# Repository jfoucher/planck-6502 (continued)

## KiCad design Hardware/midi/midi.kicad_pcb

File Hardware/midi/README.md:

## Planck 6502 MIDI board

This is a board that adds MIDI input / output to the Planck 6502 computer.

<br />This documentation is licensed under a <a rel="license" href="http://creativecommons.org/licenses/by-sa/4.0/">Creative Commons Attribution-ShareAlike 4.0 International License</a>.

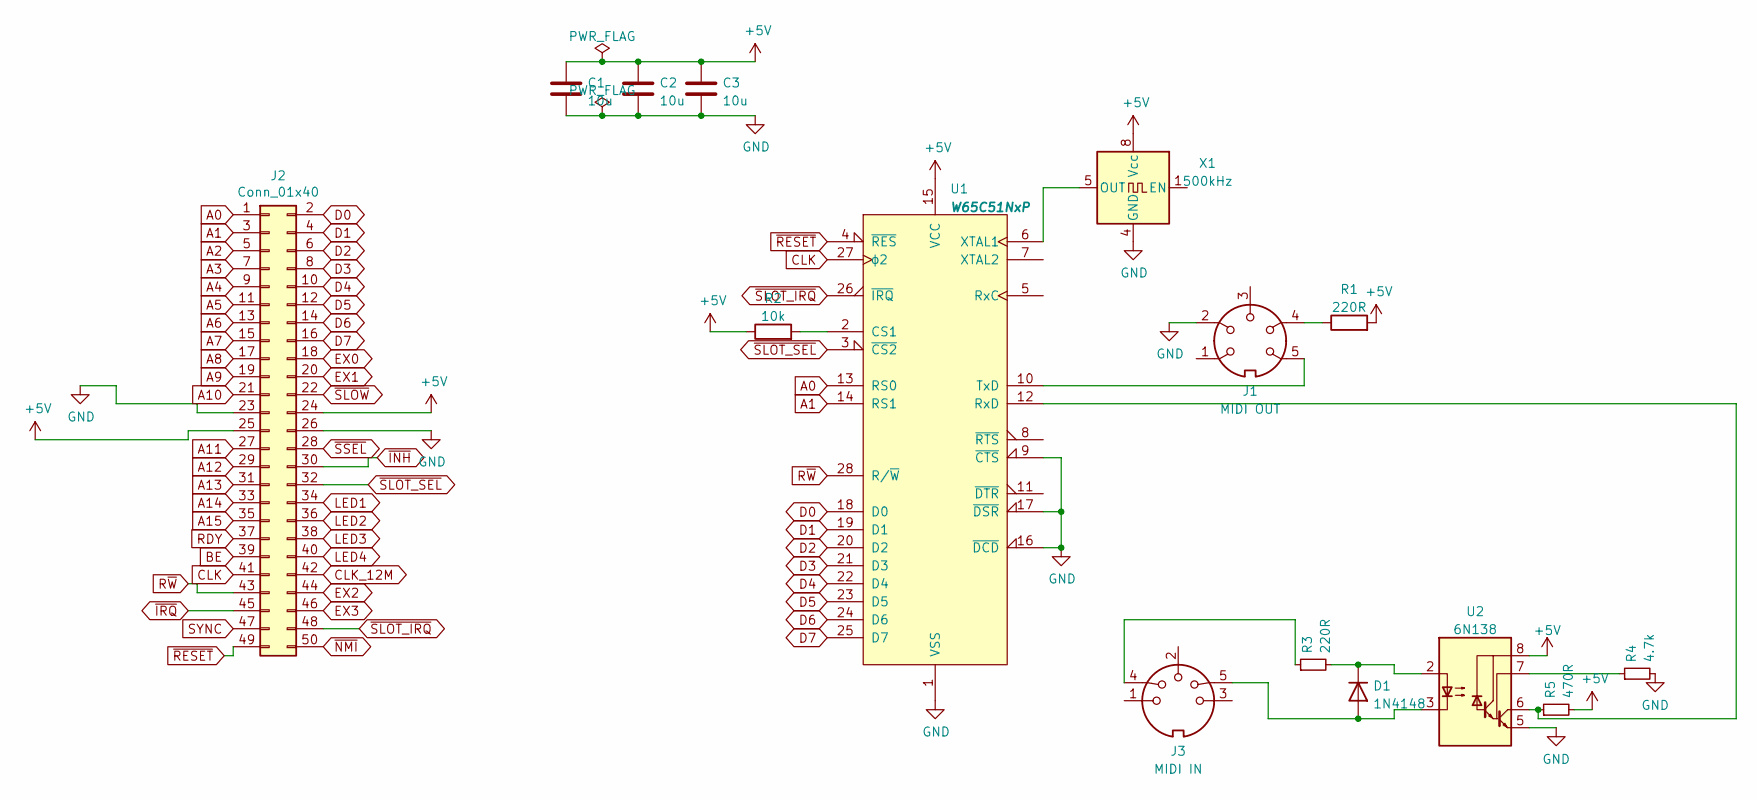
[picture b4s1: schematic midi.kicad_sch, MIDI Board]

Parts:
C1, C2, C3: 10u; C_Disc_D5.1mm_W3.2mm_P5.00mm
D1: 1N4148; D_DO-35_SOD27_P7.62mm_Horizontal
J1: MIDI OUT; din-5
J2: Conn_01x40; PinHeader_2x25_P2.54mm_Horizontal
J3: MIDI IN; din-5
R1, R3: 220R; R_Axial_DIN0207_L6.3mm_D2.5mm_P10.16mm_Horizontal
R2: 10k; R_Axial_DIN0207_L6.3mm_D2.5mm_P10.16mm_Horizontal
R4: 4.7k; R_Axial_DIN0207_L6.3mm_D2.5mm_P10.16mm_Horizontal
R5: 470R; R_Axial_DIN0207_L6.3mm_D2.5mm_P10.16mm_Horizontal
U1: W65C51NxP; DIP-40_W15.24mm_Socket
U2: 6N138; DIP-8_W7.62mm
X1: 500kHz; Oscillator_DIP-8

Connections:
+5V: C1.1, C2.1, C3.1, J2.24, J2.25, R1.2, R2.1, R5.2, U1.15 (VCC), U2.8 (VCC), X1.8 (Vcc)
A0: J2.1, U1.13 (RS0)
A1: J2.3, U1.14 (RS1)
A2: J2.5
A3: J2.7
A4: J2.9
A5: J2.11
A6: J2.13
A7: J2.15
A8: J2.17
A9: J2.19
A10: J2.21
A11: J2.27
A12: J2.29
A13: J2.31
A14: J2.33
A15: J2.35
BE: J2.39
CLK: J2.41, U1.27 (ϕ2)
CLK_12M: J2.42
D0: J2.2, U1.18 (D0)
D1: J2.4, U1.19 (D1)
D2: J2.6, U1.20 (D2)
D3: J2.8, U1.21 (D3)
D4: J2.10, U1.22 (D4)
D5: J2.12, U1.23 (D5)
D6: J2.14, U1.24 (D6)
D7: J2.16, U1.25 (D7)
EX0: J2.18
EX1: J2.20
EX2: J2.44
EX3: J2.46
GND: C1.2, C2.2, C3.2, J1.2, J2.23, J2.26, R4.2, U1.1 (VSS), U1.9 (~CTS), U1.16 (~DCD), U1.17 (~DSR), U2.5 (GND), X1.4 (GND)
LED1: J2.34
LED2: J2.36
LED3: J2.38
LED4: J2.40
unnamed: D1.1 (K), R3.2, U2.2 (C1)
unnamed: D1.2 (A), J3.5, U2.3 (C2)
unnamed: J1.4, R1.1
unnamed: J1.5, U1.10 (TxD)
unnamed: J3.4, R3.1
unnamed: R2.2, U1.2 (CS1)
unnamed: R4.1, U2.7 (VO1)
unnamed: R5.1, U1.12 (RxD), U2.6 (VO2)
unnamed: U1.6 (XTAL1), X1.5 (OUT)
RDY: J2.37
R~W: J2.43, U1.28 (R/~W)
SYNC: J2.47
~INH: J2.30
~IRQ: J2.45
~NMI: J2.50
~RESET: J2.49, U1.4 (~RES)
~SLOT_IRQ: J2.48, U1.26 (~IRQ)
~SLOT_SEL: J2.32, U1.3 (~CS2)
~SLOW: J2.22
~SSEL: J2.28

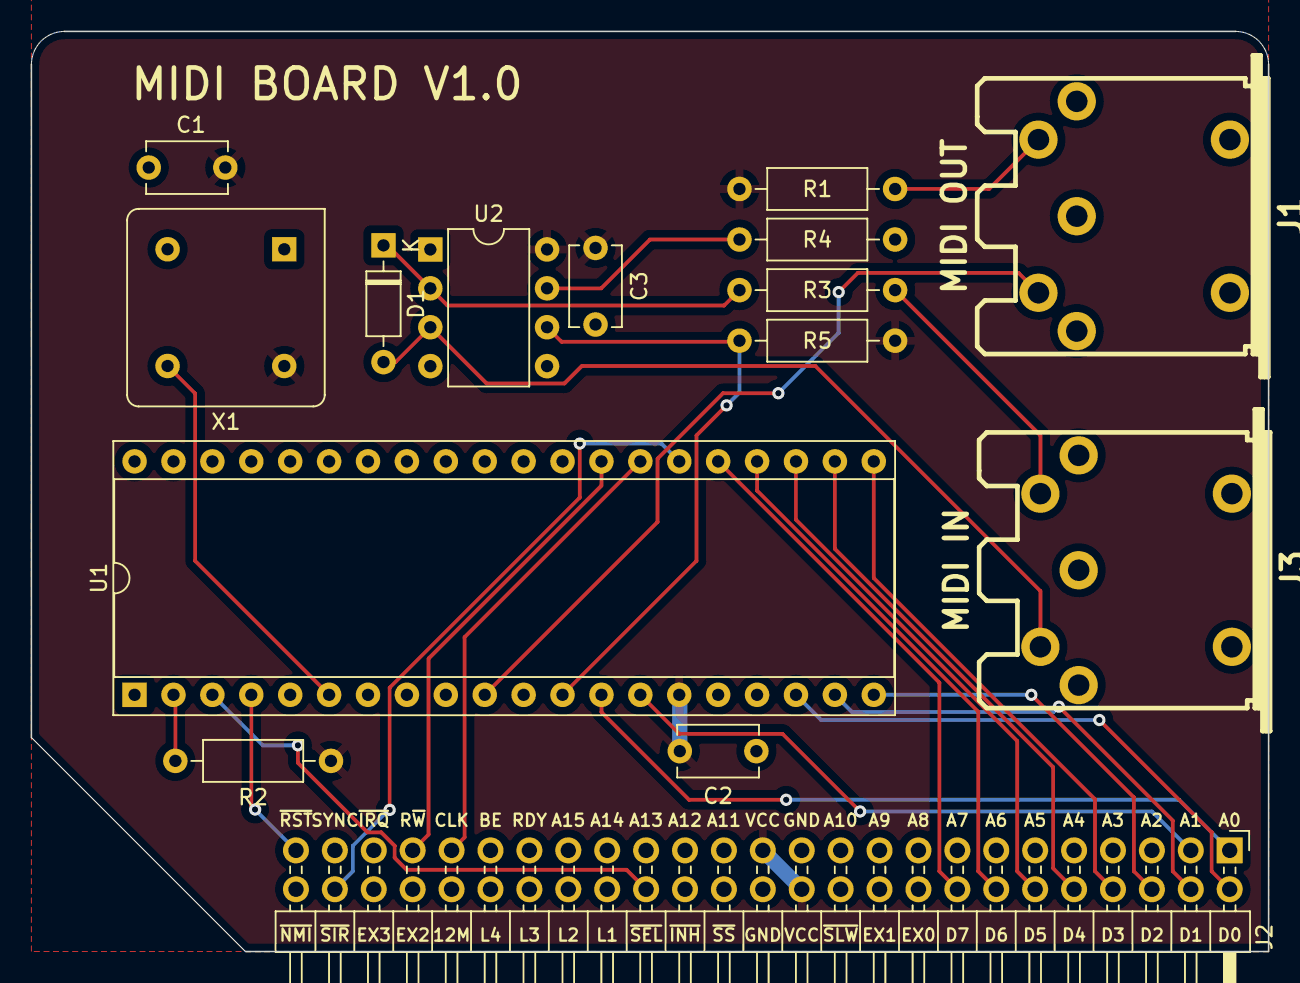
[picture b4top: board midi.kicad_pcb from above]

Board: 2 copper layers, 80.8 x 60.1 mm, 15 parts (0 on the bottom side), 26 nets.

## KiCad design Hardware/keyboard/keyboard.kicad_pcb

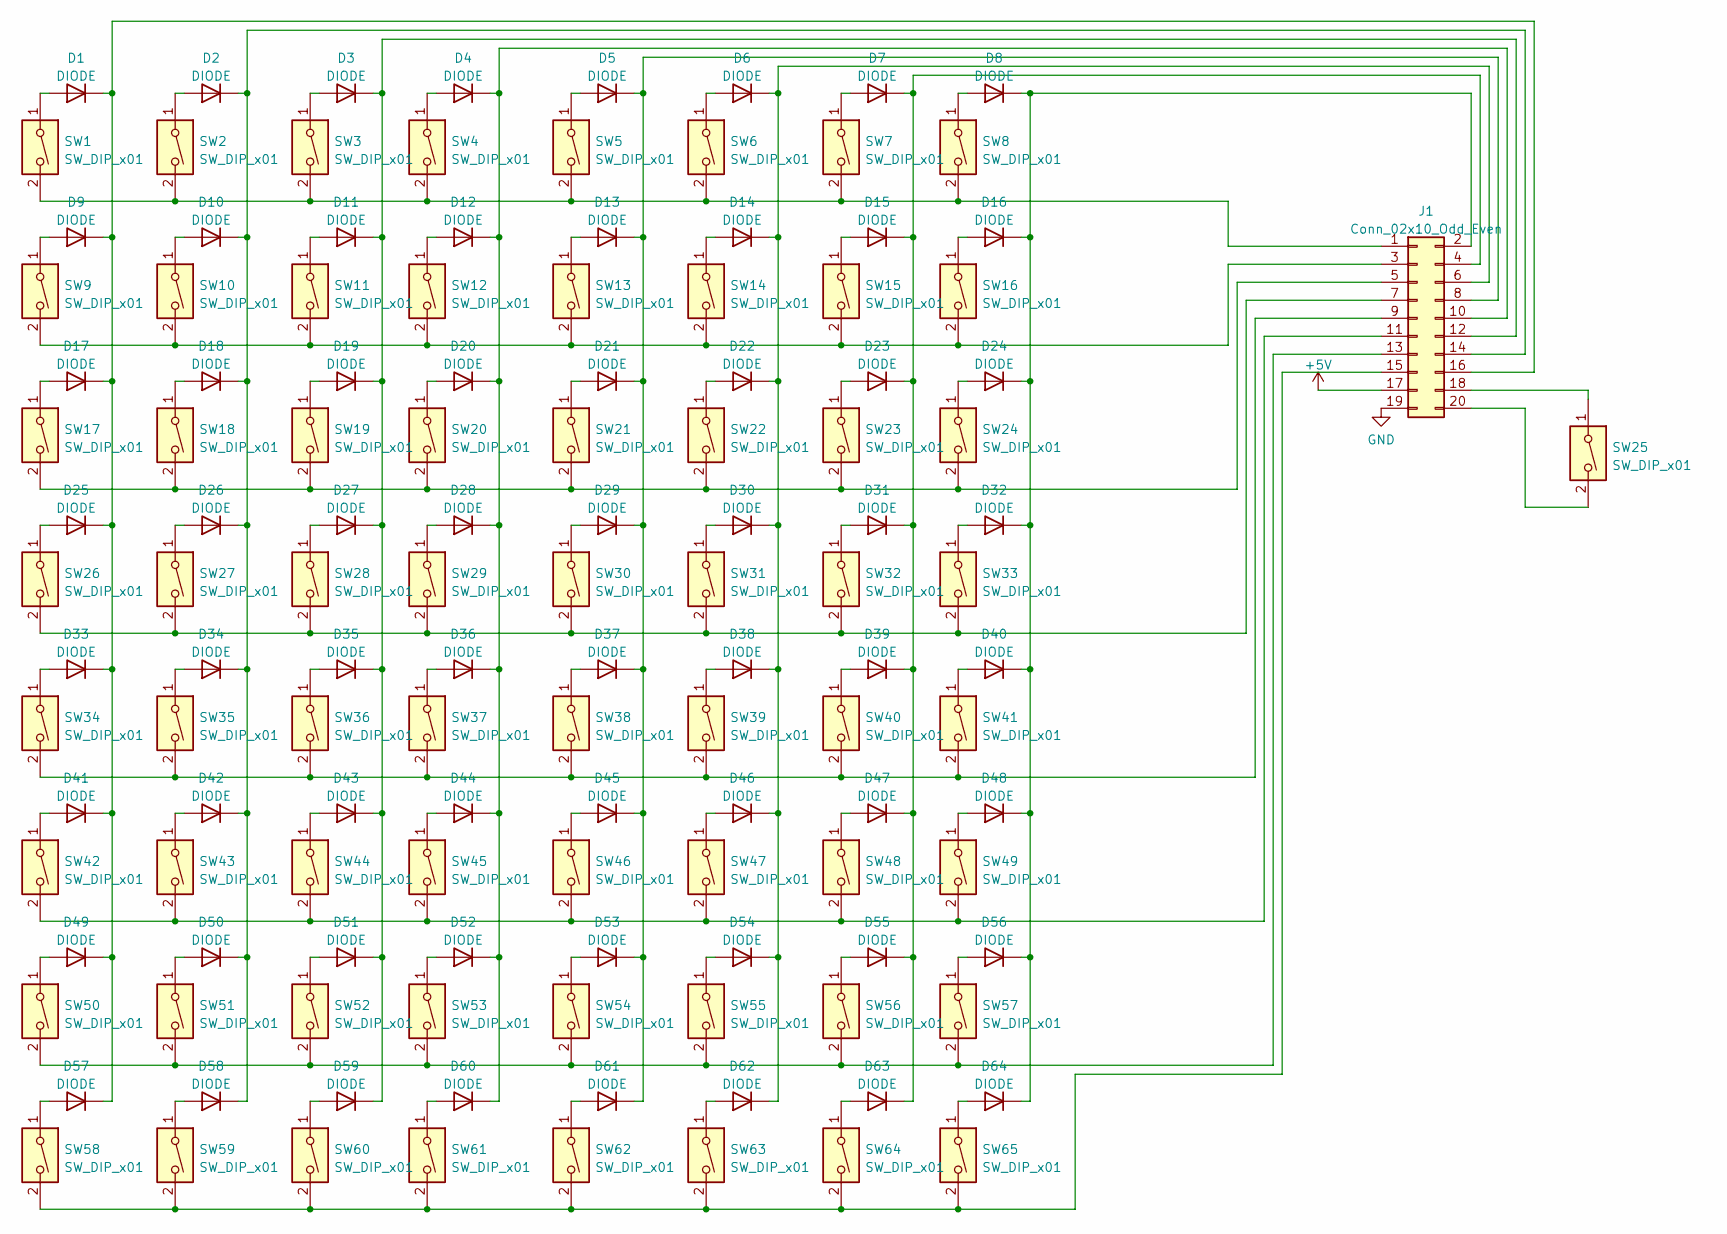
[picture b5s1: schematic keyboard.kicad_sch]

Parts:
D1, D2, D3, D4, D5, D6, D7, D8, D9, D10, D11, D12, D13, D14, D15, D16, D17, D18, D19, D20, D21, D22, D23, D24, D25, D26, D27, D28, D29, D30, D31, D32, D33, D34, D35, D36, D37, D38, D39, D40, D41, D42, D43, D44, D45, D46, D47, D48, D49, D50, D51, D52, D53, D54, D55, D56, D57, D58, D59, D60, D61, D62, D63, D64: DIODE; D_DO-35_SOD27_P7.62mm_Horizontal
J1: Conn_02x10_Odd_Even; PinHeader_2x11_P2.54mm_Horizontal
SW1, SW2, SW3, SW4, SW5, SW6, SW7, SW8, SW9, SW10, SW11, SW12, SW13, SW14, SW15, SW16, SW17, SW18, SW19, SW20, SW21, SW22, SW23, SW24, SW25, SW26, SW27, SW28, SW29, SW30, SW31, SW32, SW33, SW34, SW35, SW36, SW37, SW38, SW39, SW40, SW41, SW42, SW43, SW44, SW45, SW46, SW47, SW48, SW49, SW50, SW51, SW52, SW53, SW54, SW55, SW56, SW57, SW58, SW59, SW60, SW61, SW62, SW63, SW64, SW65: SW_DIP_x01; SW_Cherry_MX_PCB_1.00u

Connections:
+5V: J1.17
GND: J1.19
unnamed: D1.1 (K), D9.1 (K), D17.1 (K), D25.1 (K), D33.1 (K), D41.1 (K), D49.1 (K), D57.1 (K), J1.16
unnamed: D1.2 (A), SW1.1
unnamed: D2.2 (A), SW2.1
unnamed: D3.1 (K), D11.1 (K), D19.1 (K), D27.1 (K), D35.1 (K), D43.1 (K), D51.1 (K), D59.1 (K), J1.12
unnamed: D3.2 (A), SW3.1
unnamed: D4.1 (K), D12.1 (K), D20.1 (K), D28.1 (K), D36.1 (K), D44.1 (K), D52.1 (K), D60.1 (K), J1.10
unnamed: D4.2 (A), SW4.1
unnamed: D5.1 (K), D13.1 (K), D21.1 (K), D29.1 (K), D37.1 (K), D45.1 (K), D53.1 (K), D61.1 (K), J1.8
unnamed: D5.2 (A), SW5.1
unnamed: D6.1 (K), D14.1 (K), D22.1 (K), D30.1 (K), D38.1 (K), D46.1 (K), D54.1 (K), D62.1 (K), J1.6
unnamed: D6.2 (A), SW6.1
unnamed: D7.1 (K), D15.1 (K), D23.1 (K), D31.1 (K), D39.1 (K), D47.1 (K), D55.1 (K), D63.1 (K), J1.4
unnamed: D7.2 (A), SW7.1
unnamed: D8.1 (K), D16.1 (K), D24.1 (K), D32.1 (K), D40.1 (K), D48.1 (K), D56.1 (K), D64.1 (K), J1.2
unnamed: D8.2 (A), SW8.1
unnamed: D9.2 (A), SW9.1
unnamed: D2.1 (K), D10.1 (K), D18.1 (K), D26.1 (K), D34.1 (K), D42.1 (K), D50.1 (K), D58.1 (K), J1.14
unnamed: D10.2 (A), SW10.1
unnamed: D11.2 (A), SW11.1
unnamed: D12.2 (A), SW12.1
unnamed: D13.2 (A), SW13.1
unnamed: D14.2 (A), SW14.1
unnamed: D15.2 (A), SW15.1
unnamed: D16.2 (A), SW16.1
unnamed: D17.2 (A), SW17.1
unnamed: D18.2 (A), SW18.1
unnamed: D19.2 (A), SW19.1
unnamed: D20.2 (A), SW20.1
unnamed: D21.2 (A), SW21.1
unnamed: D22.2 (A), SW22.1
unnamed: D23.2 (A), SW23.1
unnamed: D24.2 (A), SW24.1
unnamed: D25.2 (A), SW26.1
unnamed: D26.2 (A), SW27.1
unnamed: D27.2 (A), SW28.1
unnamed: D28.2 (A), SW29.1
unnamed: D29.2 (A), SW30.1
unnamed: D30.2 (A), SW31.1
unnamed: D31.2 (A), SW32.1
unnamed: D32.2 (A), SW33.1
unnamed: D33.2 (A), SW34.1
unnamed: D34.2 (A), SW35.1
unnamed: D35.2 (A), SW36.1
unnamed: D36.2 (A), SW37.1
unnamed: D37.2 (A), SW38.1
unnamed: D38.2 (A), SW39.1
unnamed: D39.2 (A), SW40.1
unnamed: D40.2 (A), SW41.1
unnamed: D41.2 (A), SW42.1
unnamed: D42.2 (A), SW43.1
unnamed: D43.2 (A), SW44.1
unnamed: D44.2 (A), SW45.1
unnamed: D45.2 (A), SW46.1
unnamed: D46.2 (A), SW47.1
unnamed: D47.2 (A), SW48.1
unnamed: D48.2 (A), SW49.1
unnamed: D49.2 (A), SW50.1
unnamed: D50.2 (A), SW51.1
unnamed: D51.2 (A), SW52.1
unnamed: D52.2 (A), SW53.1
unnamed: D53.2 (A), SW54.1
unnamed: D54.2 (A), SW55.1
unnamed: D55.2 (A), SW56.1
unnamed: D56.2 (A), SW57.1
unnamed: D57.2 (A), SW58.1
unnamed: D58.2 (A), SW59.1
unnamed: D59.2 (A), SW60.1
unnamed: D60.2 (A), SW61.1
unnamed: D61.2 (A), SW62.1
unnamed: D62.2 (A), SW63.1
unnamed: D63.2 (A), SW64.1
unnamed: D64.2 (A), SW65.1
unnamed: J1.1, SW1.2, SW2.2, SW3.2, SW4.2, SW5.2, SW6.2, SW7.2, SW8.2
unnamed: J1.3, SW9.2, SW10.2, SW11.2, SW12.2, SW13.2, SW14.2, SW15.2, SW16.2
unnamed: J1.5, SW17.2, SW18.2, SW19.2, SW20.2, SW21.2, SW22.2, SW23.2, SW24.2
unnamed: J1.7, SW26.2, SW27.2, SW28.2, SW29.2, SW30.2, SW31.2, SW32.2, SW33.2
unnamed: J1.9, SW34.2, SW35.2, SW36.2, SW37.2, SW38.2, SW39.2, SW40.2, SW41.2
unnamed: J1.11, SW42.2, SW43.2, SW44.2, SW45.2, SW46.2, SW47.2, SW48.2, SW49.2
unnamed: J1.13, SW50.2, SW51.2, SW52.2, SW53.2, SW54.2, SW55.2, SW56.2, SW57.2
unnamed: J1.15, SW58.2, SW59.2, SW60.2, SW61.2, SW62.2, SW63.2, SW64.2, SW65.2
unnamed: J1.18, SW25.1
unnamed: J1.20, SW25.2

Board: 2 copper layers, 130 parts (0 on the bottom side), 82 nets, no tracks yet.

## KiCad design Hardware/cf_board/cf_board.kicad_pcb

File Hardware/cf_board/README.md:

## Compact Flash board

This board allows adding one Compact Flash (CF) card to the Planck computer. This gives mass storage capabilities to the computer.

The file system is not complete yet, but will probably be FAT16 to allow interoperability with PCs

You will be able to save and load files. 

It will be possible to load forth words and assembly code from the compact flash card.

You can [download the schematic](https://planck6502.com/fabrication/cf_board-schematic.pdf) and the [gerber files](https://planck6502.com/fabrication/cf_board-zip.zip)

[Documentation](https://planck6502.com/Hardware/cf/)

<br />This documentation is licensed under a <a rel="license" href="http://creativecommons.org/licenses/by-sa/4.0/">Creative Commons Attribution-ShareAlike 4.0 International License</a>.

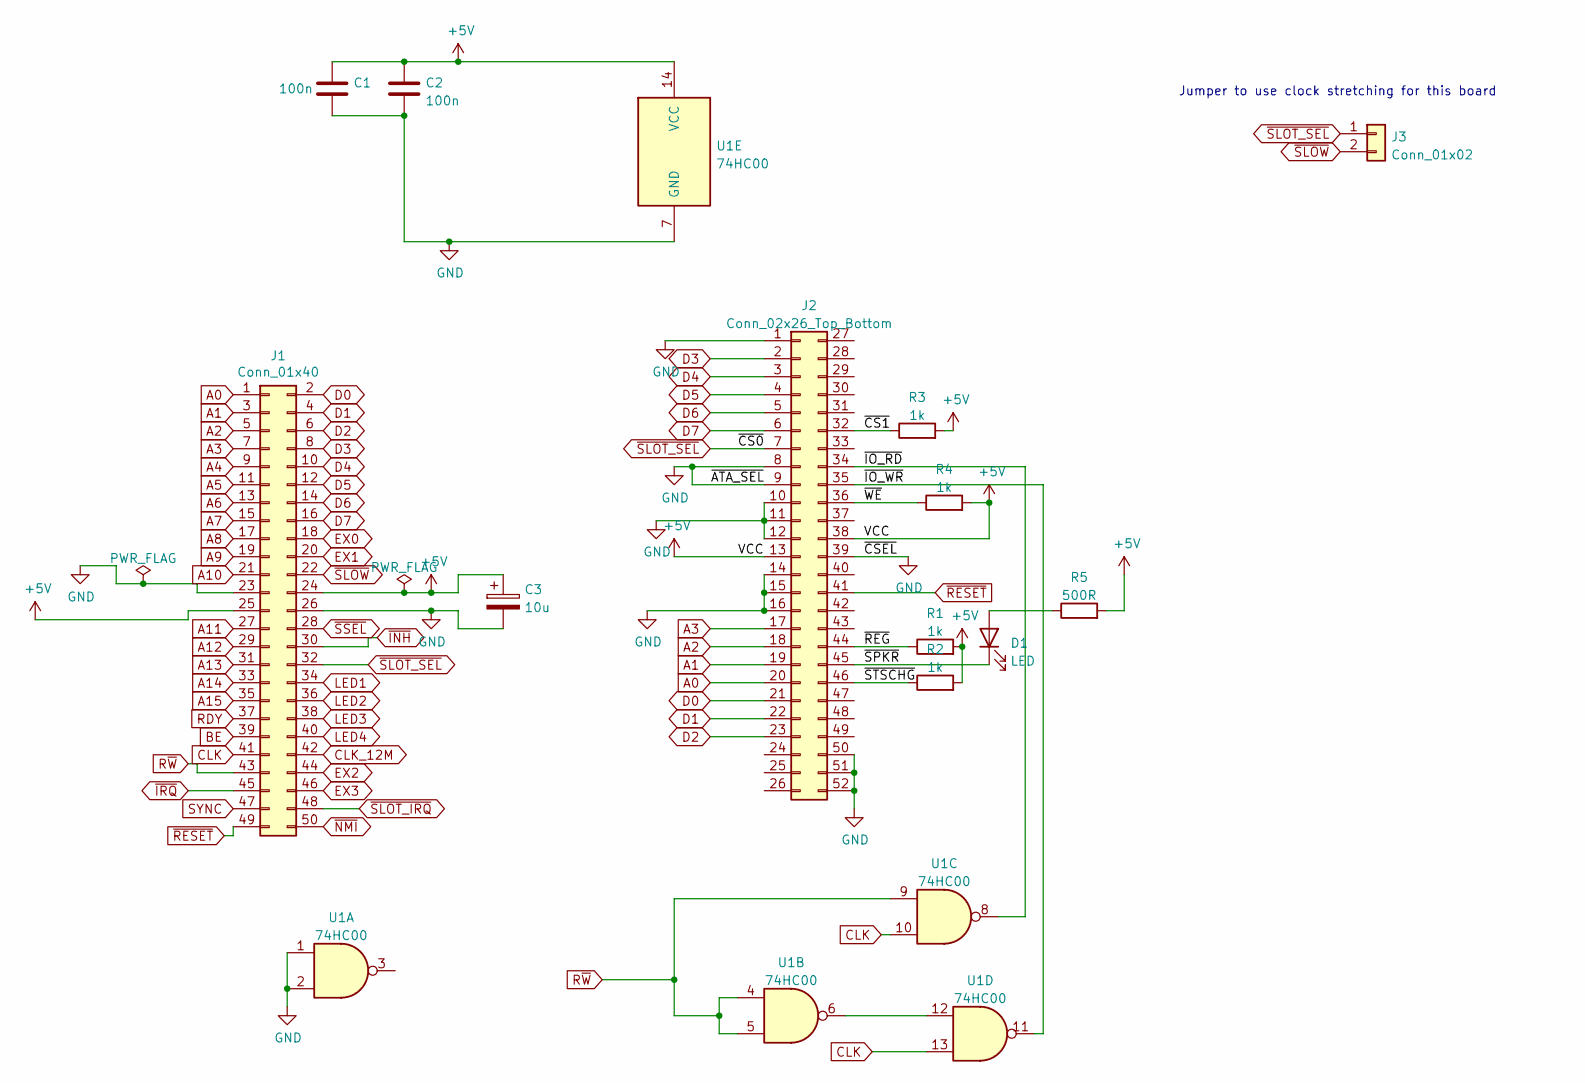
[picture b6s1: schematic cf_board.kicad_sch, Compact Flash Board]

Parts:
C1, C2: 100n; C_Disc_D5.0mm_W2.5mm_P5.00mm
C3: 10u; CP_Radial_D5.0mm_P2.50mm
D1: LED; LED_D3.0mm
J1: Conn_01x40; PinHeader_2x25_P2.54mm_Horizontal
J2: Conn_02x26_Top_Bottom; SD-SMD_CFH-L3C1LBL01MN0
J3: Conn_01x02; PinHeader_1x02_P2.54mm_Vertical
R1, R2, R3, R4: 1k; R_Axial_DIN0207_L6.3mm_D2.5mm_P10.16mm_Horizontal
R5: 500R; R_Axial_DIN0207_L6.3mm_D2.5mm_P10.16mm_Horizontal
U1: 74HC00; DIP-14_W7.62mm_Socket

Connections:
+5V: C1.1, C2.1, C3.1, J1.24, J1.25, J2.13, J2.38, R1.2, R2.2, R3.2, R4.2, R5.2, U1.14 (VCC)
/~CS1: J2.32, R3.1
/~IO_RD: J2.34, U1.8
/~IO_WR: J2.35, U1.11
/~REG: J2.44, R1.1
/~SPKR: D1.1 (K), J2.45
/~STSCHG: J2.46, R2.1
/~WE: J2.36, R4.1
A0: J1.1, J2.20
A1: J1.3, J2.19
A2: J1.5, J2.18
A3: J1.7, J2.17
A4: J1.9
A5: J1.11
A6: J1.13
A7: J1.15
A8: J1.17
A9: J1.19
A10: J1.21
A11: J1.27
A12: J1.29
A13: J1.31
A14: J1.33
A15: J1.35
BE: J1.39
CLK: J1.41, U1.10, U1.13
CLK_12M: J1.42
D0: J1.2, J2.21
D1: J1.4, J2.22
D2: J1.6, J2.23
D3: J1.8, J2.2
D4: J1.10, J2.3
D5: J1.12, J2.4
D6: J1.14, J2.5
D7: J1.16, J2.6
EX0: J1.18
EX1: J1.20
EX2: J1.44
EX3: J1.46
GND: C1.2, C2.2, C3.2, J1.23, J1.26, J2.1, J2.8, J2.9, J2.10, J2.11, J2.12, J2.14, J2.15, J2.16, J2.39, J2.50, J2.51, J2.52, U1.1, U1.2, U1.7 (GND)
LED1: J1.34
LED2: J1.36
LED3: J1.38
LED4: J1.40
unnamed: D1.2 (A), R5.1
unnamed: U1.6, U1.12
RDY: J1.37
R~W: J1.43, U1.4, U1.5, U1.9
SYNC: J1.47
~INH: J1.30
~IRQ: J1.45
~NMI: J1.50
~RESET: J1.49, J2.41
~SLOT_IRQ: J1.48
~SLOT_SEL: J1.32, J2.7, J3.1
~SLOW: J1.22, J3.2
~SSEL: J1.28

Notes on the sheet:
Jumper to use clock stretching for this board

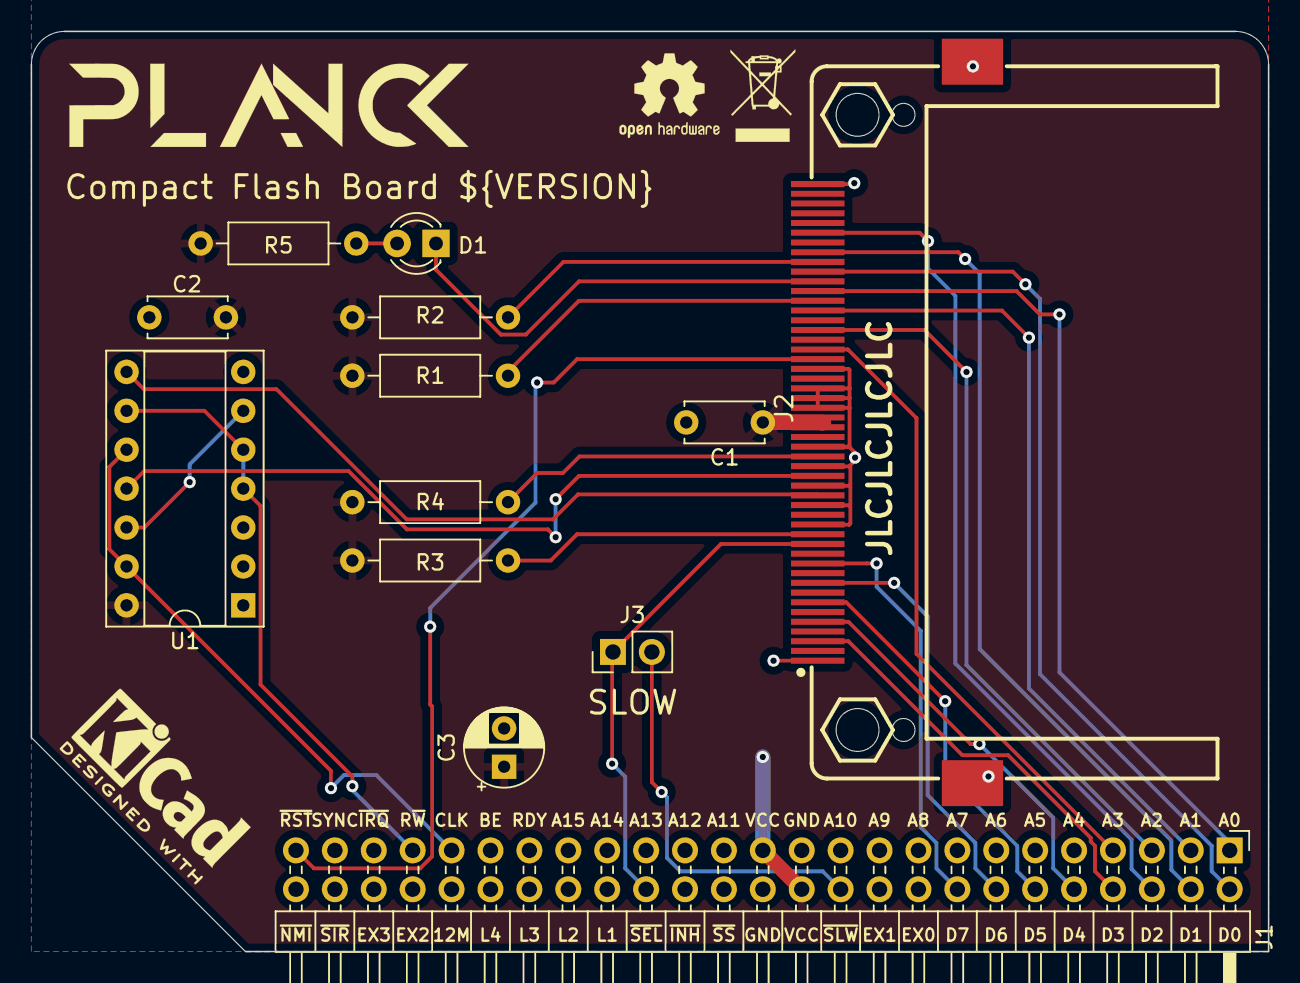
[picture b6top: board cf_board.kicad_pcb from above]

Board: 2 copper layers, 80.8 x 60.1 mm, 13 parts (0 on the bottom side), 28 nets.

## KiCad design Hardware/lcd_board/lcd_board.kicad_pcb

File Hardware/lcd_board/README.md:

## Planck 6502 LCD board

This board allows adding a HD44780 based LCD to the Planck computer.

This is what the board looks like at the moment:

You can [download the schematic](https://planck6502.com/fabrication/lcd_board-schematic.pdf) and the [gerber files](https://planck6502.com/fabrication/lcd_board-zip.zip)

[Documentation](https://planck6502.com/Hardware/lcd/)

<br />This documentation is licensed under a <a rel="license" href="http://creativecommons.org/licenses/by-sa/4.0/">Creative Commons Attribution-ShareAlike 4.0 International License</a>.

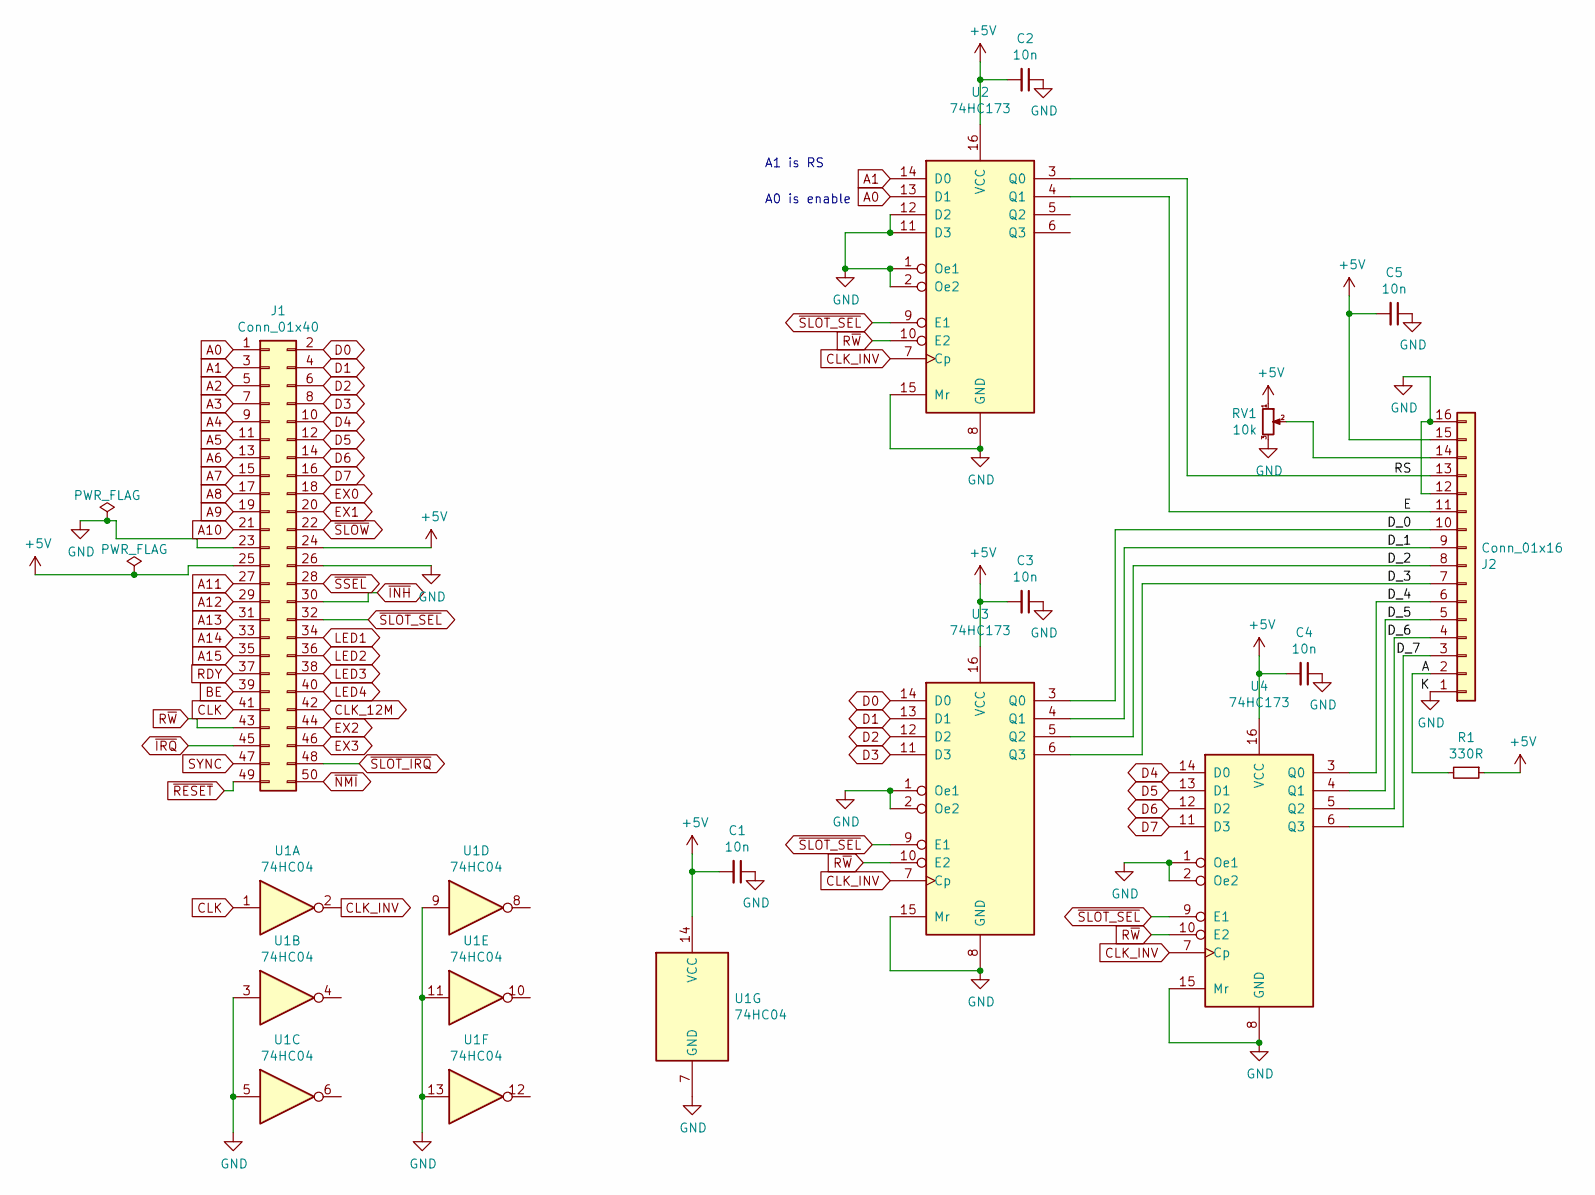
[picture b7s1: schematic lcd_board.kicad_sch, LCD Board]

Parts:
C1, C2, C3, C4, C5: 10n; C_Disc_D4.3mm_W1.9mm_P5.00mm
J1: Conn_01x40; PinHeader_2x25_P2.54mm_Horizontal
J2: Conn_01x16; PinSocket_1x16_P2.54mm_Horizontal
R1: 330R; R_Axial_DIN0207_L6.3mm_D2.5mm_P10.16mm_Horizontal
RV1: 10k; Potentiometer_Piher_PT-6-V_Vertical
U1: 74HC04; DIP-14_W7.62mm_Socket
U2, U3, U4: 74HC173; DIP-16_W7.62mm_Socket

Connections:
+5V: C1.2, C2.2, C3.2, C4.2, C5.2, J1.24, J1.25, J2.15, R1.1, RV1.1, U1.14 (VCC), U2.16 (VCC), U3.16 (VCC), U4.16 (VCC)
/A: J2.2, R1.2
/D_0: J2.10, U3.3 (Q0)
/D_1: J2.9, U3.4 (Q1)
/D_2: J2.8, U3.5 (Q2)
/D_3: J2.7, U3.6 (Q3)
/D_4: J2.6, U4.3 (Q0)
/D_5: J2.5, U4.4 (Q1)
/D_6: J2.4, U4.5 (Q2)
/D_7: J2.3, U4.6 (Q3)
/E: J2.11, U2.4 (Q1)
/RS: J2.13, U2.3 (Q0)
A0: J1.1, U2.13 (D1)
A1: J1.3, U2.14 (D0)
A2: J1.5
A3: J1.7
A4: J1.9
A5: J1.11
A6: J1.13
A7: J1.15
A8: J1.17
A9: J1.19
A10: J1.21
A11: J1.27
A12: J1.29
A13: J1.31
A14: J1.33
A15: J1.35
BE: J1.39
CLK: J1.41, U1.1
CLK_12M: J1.42
CLK_INV: U1.2, U2.7 (Cp), U3.7 (Cp), U4.7 (Cp)
D0: J1.2, U3.14 (D0)
D1: J1.4, U3.13 (D1)
D2: J1.6, U3.12 (D2)
D3: J1.8, U3.11 (D3)
D4: J1.10, U4.14 (D0)
D5: J1.12, U4.13 (D1)
D6: J1.14, U4.12 (D2)
D7: J1.16, U4.11 (D3)
EX0: J1.18
EX1: J1.20
EX2: J1.44
EX3: J1.46
GND: C1.1, C2.1, C3.1, C4.1, C5.1, J1.23, J1.26, J2.1, J2.12, J2.16, RV1.3, U1.3, U1.5, U1.7 (GND), U1.9, U1.11, U1.13, U2.1 (Oe1), U2.2 (Oe2), U2.8 (GND), U2.11 (D3), U2.12 (D2), U2.15 (Mr), U3.1 (Oe1), U3.2 (Oe2), U3.8 (GND), U3.15 (Mr), U4.1 (Oe1), U4.2 (Oe2), U4.8 (GND), U4.15 (Mr)
LED1: J1.34
LED2: J1.36
LED3: J1.38
LED4: J1.40
unnamed: J2.14, RV1.2
RDY: J1.37
R~W: J1.43, U2.10 (E2), U3.10 (E2), U4.10 (E2)
SYNC: J1.47
~INH: J1.30
~IRQ: J1.45
~NMI: J1.50
~RESET: J1.49
~SLOT_IRQ: J1.48
~SLOT_SEL: J1.32, U2.9 (E1), U3.9 (E1), U4.9 (E1)
~SLOW: J1.22
~SSEL: J1.28

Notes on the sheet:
A0 is enable
A1 is RS

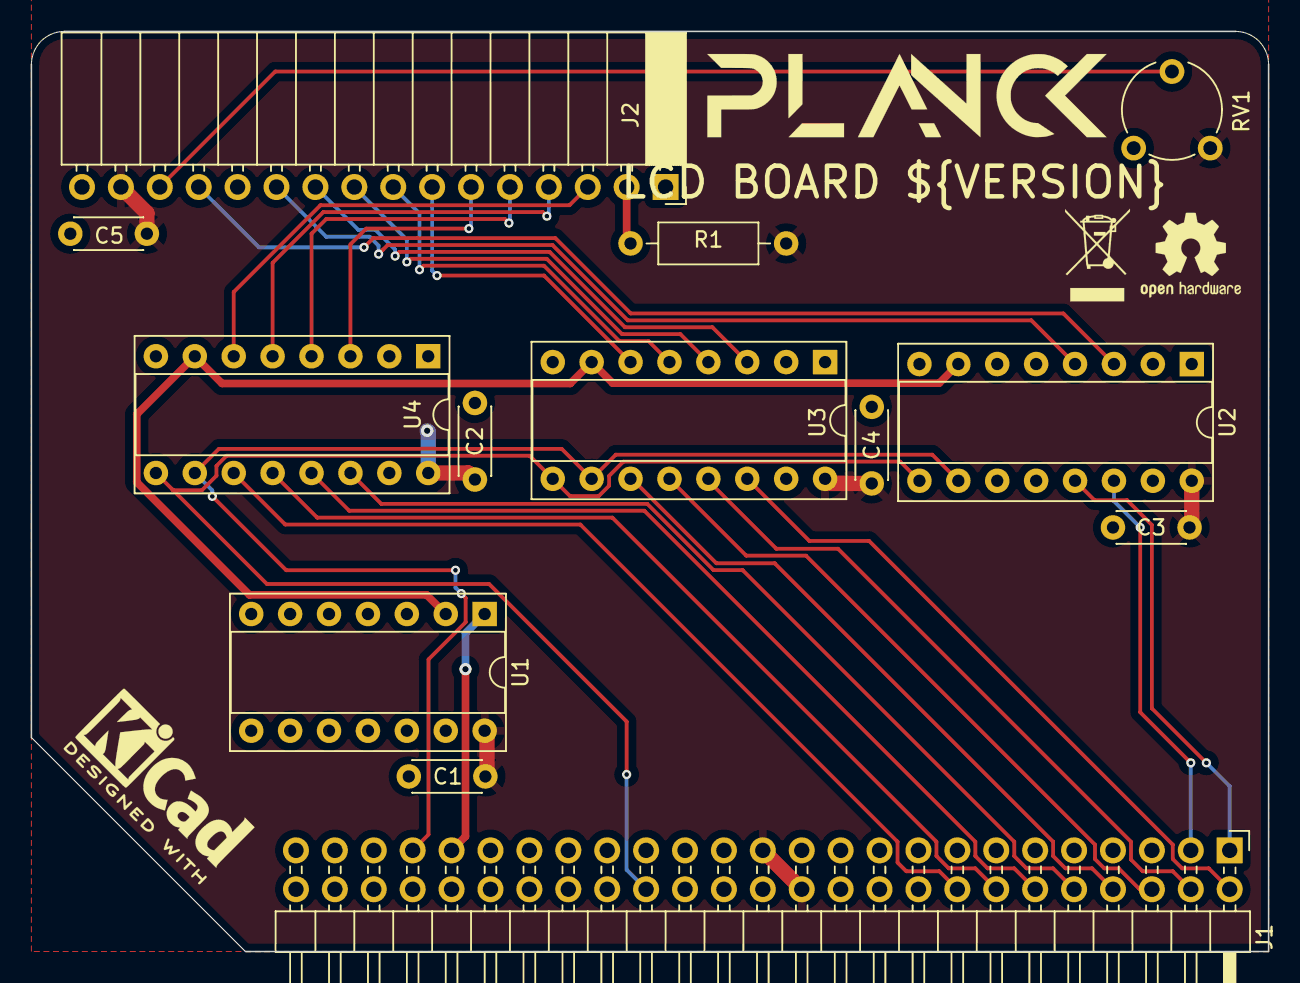
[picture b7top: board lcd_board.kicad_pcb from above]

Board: 2 copper layers, 80.8 x 60.1 mm, 13 parts (0 on the bottom side), 28 nets.

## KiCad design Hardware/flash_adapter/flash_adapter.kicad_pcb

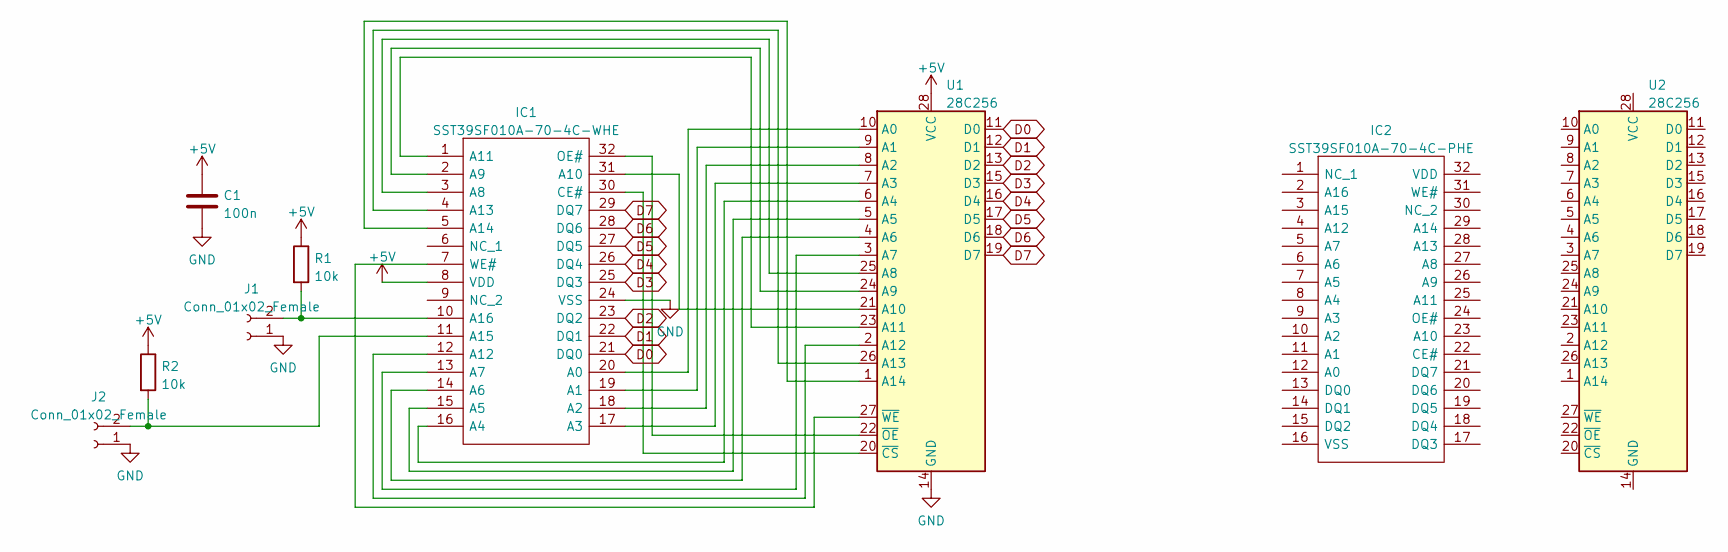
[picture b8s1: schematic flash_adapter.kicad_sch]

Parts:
C1: 100n; C_0805_2012Metric_Pad1.18x1.45mm_HandSolder
IC1: SST39SF010A-70-4C-WHE; SOP50P1400X120-32N; Mouser Part Number 804-39SF010A7CWHE
IC2: SST39SF010A-70-4C-PHE; DIP1556W56P254L4191H508Q32N; Mouser Part Number 804-39SF010A7CPHE
J1, J2: Conn_01x02_Female; SolderJumper-2_P1.3mm_Open_RoundedPad1.0x1.5mm
R1, R2: 10k; R_0805_2012Metric_Pad1.20x1.40mm_HandSolder
U1: 28C256; DIP-28_W15.24mm_Socket
U2: 28C256; PLCC-32_THT-Socket

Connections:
+5V: C1.1, IC1.8 (VDD), R1.1, R2.1, U1.28 (VCC)
D0: IC1.21 (DQ0), U1.11 (D0)
D1: IC1.22 (DQ1), U1.12 (D1)
D2: IC1.23 (DQ2), U1.13 (D2)
D3: IC1.25 (DQ3), U1.15 (D3)
D4: IC1.26 (DQ4), U1.16 (D4)
D5: IC1.27 (DQ5), U1.17 (D5)
D6: IC1.28 (DQ6), U1.18 (D6)
D7: IC1.29 (DQ7), U1.19 (D7)
GND: C1.2, IC1.24 (VSS), J1.1, J2.1, U1.14 (GND)
unnamed: IC1.1 (A11), U1.23 (A11)
unnamed: IC1.2 (A9), U1.24 (A9)
unnamed: IC1.3 (A8), U1.25 (A8)
unnamed: IC1.4 (A13), U1.26 (A13)
unnamed: IC1.5 (A14), U1.1 (A14)
unnamed: IC1.7 (WE#), U1.27 (~WE)
unnamed: IC1.10 (A16), J1.2, R1.2
unnamed: IC1.11 (A15), J2.2, R2.2
unnamed: IC1.12 (A12), U1.2 (A12)
unnamed: IC1.13 (A7), U1.3 (A7)
unnamed: IC1.14 (A6), U1.4 (A6)
unnamed: IC1.15 (A5), U1.5 (A5)
unnamed: IC1.16 (A4), U1.6 (A4)
unnamed: IC1.17 (A3), U1.7 (A3)
unnamed: IC1.18 (A2), U1.8 (A2)
unnamed: IC1.19 (A1), U1.9 (A1)
unnamed: IC1.20 (A0), U1.10 (A0)
unnamed: IC1.30 (CE#), U1.20 (~CS)
unnamed: IC1.31 (A10), U1.21 (A10)
unnamed: IC1.32 (OE#), U1.22 (~OE)

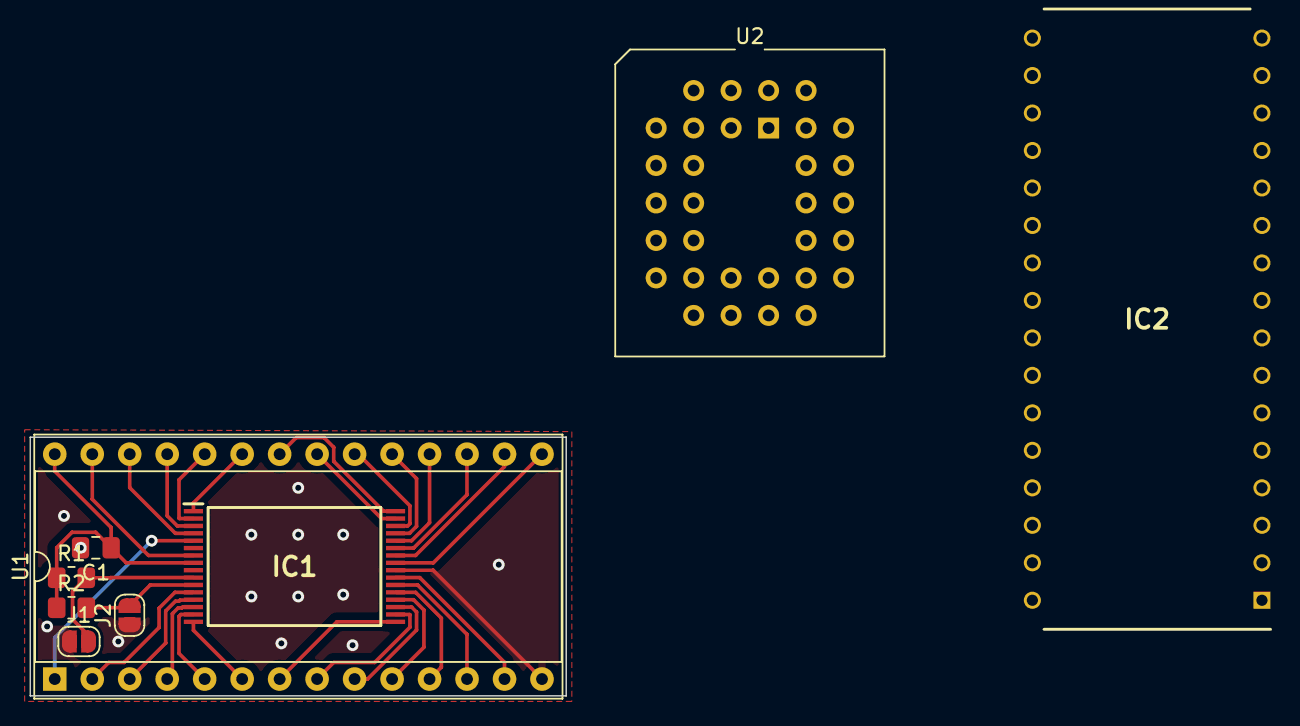
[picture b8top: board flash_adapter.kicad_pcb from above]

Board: 2 copper layers, 36.3 x 17.5 mm, 9 parts (0 on the bottom side), 30 nets.
